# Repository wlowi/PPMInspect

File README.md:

# PPMInspect

Ein Tool zur Analyse von PPM Signalen.  

## Features

- PPM Decoder bis 16 Kanäle mit Anzeige der Timing Werte für jeden Kanal
- PWM Decoder
- Einfaches Voltmeter
- Oszilloskop mit 1kHz bis 100kHz Samplingrate
- Trigger (Freilaufend, ansteigende Flanke, abfallende Flanke)
- Zuschaltbares oversampling
- Einstellbarer Triggerlevel
- Triggerverzögerung bis 9900 Microsekunden.

Zur [Bedienungsanleitung](MANUAL.md)

## Handware

- 1 Arduino Nano
- 1 OLED Display 1.3" (SH1106 Controller)
- 3 Taster (RAFI Kurzhubtaster RACON 8 mit Stößel 7.5mm Höhe 8.2mm)
- 1 Z-Diode 4.7V
- 3 Widerstände 1/8 W 47k
- 2 Widerstände 1/8 W 100k
- 1 Elko 100uF 16V
- Stecker nach Wahl (Gebogene Pfostenleiste)

## Verwendete Libraries

Folgende Libraries werden benötigt und über die Arduino IDE installiert:

- SSD1306Ascii

## Arduino Nano Ports

- LCD SCK:   A5 (Port PC5 SCL)
- LCD SDA:   A4 (Port PC4 SDA)
- Taster 1:   5 (Port PD5 PCINT21 PCI2)
- Taster 2:   6 (Port PD6 PCINT22 PCI2)
- Taster 3:   7 (Port PD7 PCINT23 PCI2)
- Analog In: A3 (Port PC3)
- PPM In:     8 (Port PB0 ICP1)
- Vcc:       A0
   
## Timer

- Timer 0:     8 bit       Arduino micros() millis() delay()...
- Timer 1:    16 bit       PPM Timing (See PPM.cpp)

## Verzeichnisse

CAD - dxf und FreeCAD Model für ein Gehäuse  
doc - Zur Dokumentation  
PCB - KiCAD Schaltplan und Platinenlayout  
PPMGenerate_DELAY - PPM Test Generator mit Verzögerungsschleife  
PPMGenerate_ISR - PPM Test Generator über Interrupts  
PPMGenerate_PWM - PPM Test Generator über Hardware-PWM  
PPMInspect - Der Source Code  

## Und Sonst...

### Wird anstelle eines SH1106 ein SSD1306 Display Controller verwendet muss in PPMInspect.ino Zeile 98 von:

textUI.setDisplay(new TextUILcdSSD1306( &SH1106_128x64 )); \
geändert werden in: \
textUI.setDisplay(new TextUILcdSSD1306( &Adafruit128x64 ));

### Genauigkeit PPM Scan

- Servotiming pro Kanal: +/- 1 Microsekunde
- Puls: +/- 1 Microsekunde
- Frame: +/- 1 Microsekunde

## TODO

- Nix zur Zeit

## History

0.10.0: PWM Decoder\
0.9.17: User Interface aktualisiert\
0.9.16: PPM Erzeugung verbessert\
0.9.15: Frame Genauigkeit verbessert\
0.9.14: Min/max Werte im Voltmeter

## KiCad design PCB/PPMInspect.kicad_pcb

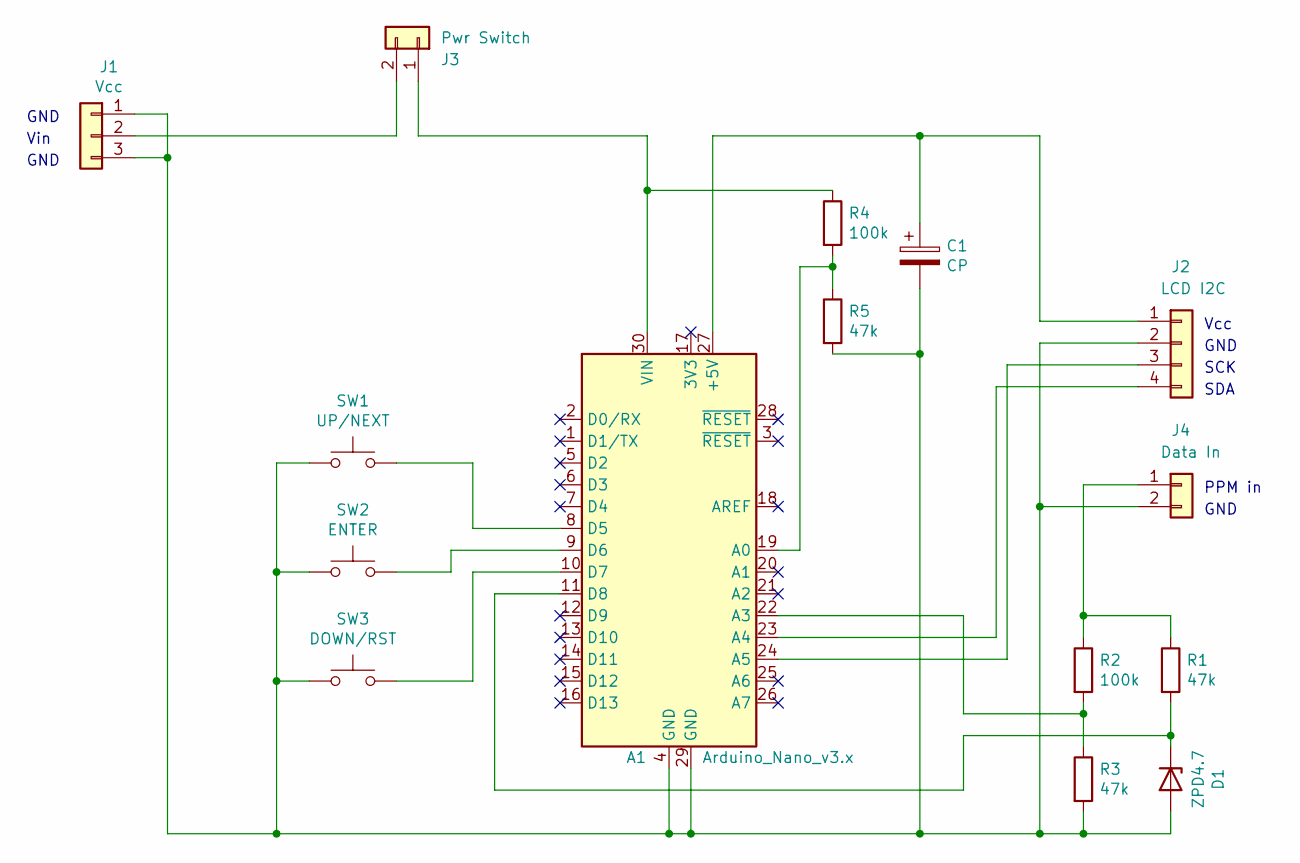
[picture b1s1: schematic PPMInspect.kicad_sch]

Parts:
A1: Arduino_Nano_v3.x; Arduino_Nano
C1: CP; CP_Radial_D6.3mm_P2.50mm
D1: ZPD4.7; D_DO-35_SOD27_P10.16mm_Horizontal
J1: Vcc; PinHeader_1x03_P2.54mm_Horizontal
J2: LCD I2C; PinSocket_1x04_P2.54mm_Vertical
J3: Pwr Switch; PinHeader_1x02_P2.54mm_Horizontal
J4: Data In; PinHeader_1x02_P2.54mm_Horizontal
R1, R3, R5: 47k; R_Axial_DIN0207_L6.3mm_D2.5mm_P10.16mm_Horizontal
R2, R4: 100k; R_Axial_DIN0207_L6.3mm_D2.5mm_P10.16mm_Horizontal
SW1: UP/NEXT; SW_PUSH_6mm
SW2: ENTER; SW_PUSH_6mm
SW3: DOWN/RST; SW_PUSH_6mm

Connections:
unnamed: A1.8 (D5), SW1.2
unnamed: A1.9 (D6), SW2.2
unnamed: A1.10 (D7), SW3.2
unnamed: A1.11 (D8), D1.1 (K), R1.2
unnamed: A1.19 (A0), R4.2, R5.1
unnamed: A1.22 (A3), R2.2, R3.1
unnamed: A1.23 (A4), J2.4
unnamed: A1.24 (A5), J2.3
unnamed: A1.27 (+5V), C1.1, J2.1
unnamed: A1.4 (GND), A1.29 (GND), C1.2, D1.2 (A), J1.1, J1.3, J2.2, J4.2, R3.2, R5.2, SW1.1, SW2.1, SW3.1
unnamed: A1.30 (VIN), J3.1, R4.1
unnamed: J1.2, J3.2
unnamed: J4.1, R1.1, R2.1

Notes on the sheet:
SDA
Vin
SCK
GND
PPM in
Vcc

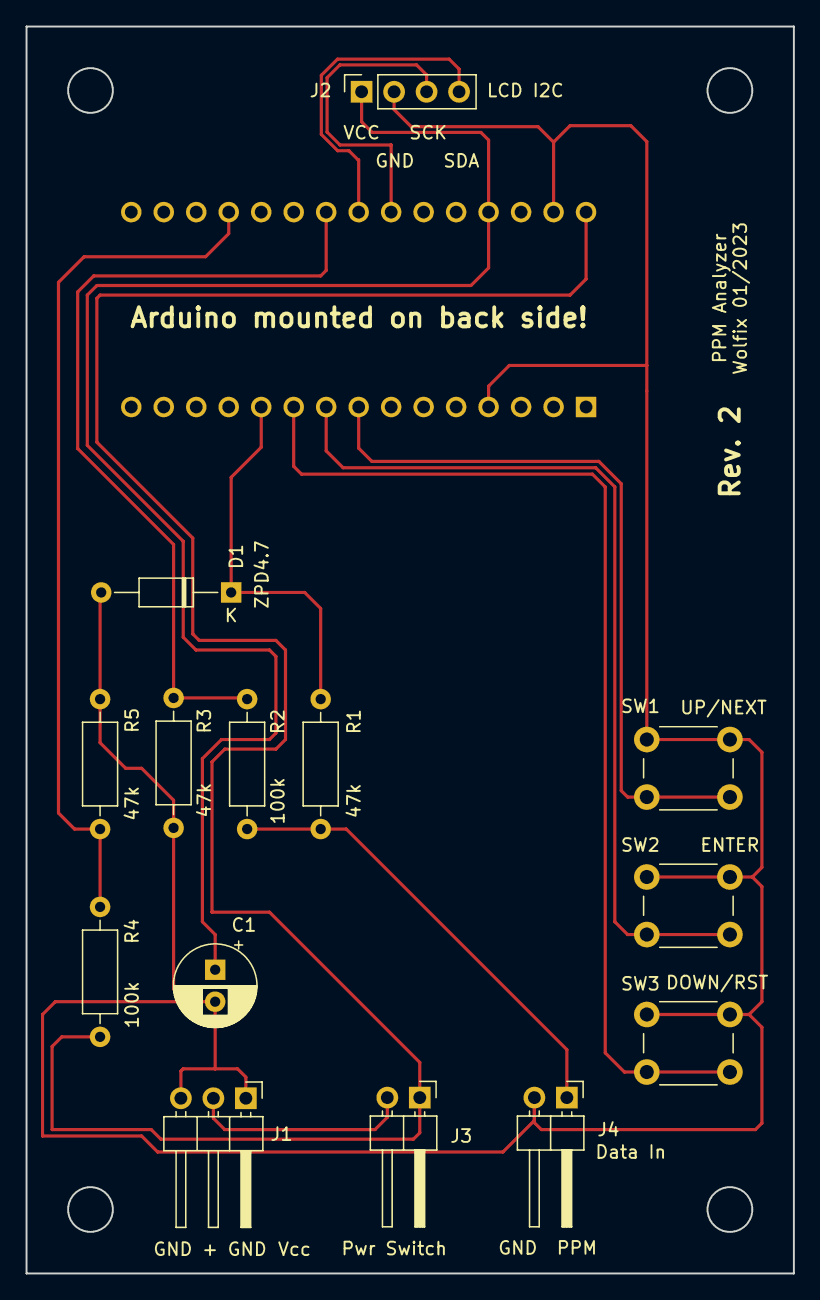
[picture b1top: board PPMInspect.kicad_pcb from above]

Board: 2 copper layers, 60.0 x 97.5 mm, 15 parts (1 on the bottom side), 13 nets.

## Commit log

2023-03-25 V0.9.13
2023-03-26 Required library and additional notes.
2023-03-26 Fix off by one in PPMGenerate_PWM.ino
2023-04-01 Voltmeter min/max. Vcc Monitor. V0.9.14
2023-04-01 Adjusted Vcc Monitor interval to 10 sec.
2023-04-08 Update to last TextUI Version.
2023-04-08 Fixed unaccuracy in frame time computation. V0.9.15
2023-04-09 PPMGenerate_PWM for Nano. Minor changes. V0.9.16
2023-04-20 README.md formatting.
2023-10-22 Microscope grid fix. KiCad new version. V0.9.18
2023-10-22 Microscope V adjusted. Y Range added.
2023-12-31 Free memory by copying text from progmem. V0.9.19
2024-01-01 PWM scan. V0.10.0
2024-01-02 Minor memory changes. V0.10.1
2024-01-02 PWM scope display. V0.10.2
2024-01-03 Compute and display duty cycle. V0.10.3
2024-01-03 Remove freq from pwm set.
2024-01-05 Documentation updated.
